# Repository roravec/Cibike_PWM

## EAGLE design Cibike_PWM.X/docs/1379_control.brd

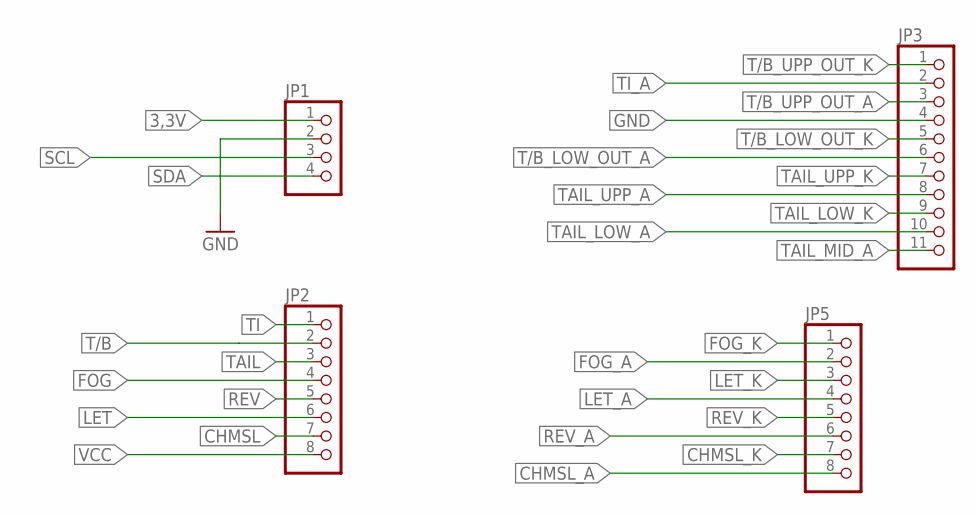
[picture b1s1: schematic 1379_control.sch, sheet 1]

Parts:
JP1: PINHD-1X4; 1X04
JP2, JP5: PINHD-1X8; 1X08
JP3: PINHD-1X11; 1X11

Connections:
3,3V: JP1.1; also elsewhere on the board
CHMSL: JP2.7; also elsewhere on the board
CHMSL_A: JP5.8; also elsewhere on the board
CHMSL_K: JP5.7; also elsewhere on the board
FOG: JP2.4; also elsewhere on the board
FOG_A: JP5.2; also elsewhere on the board
FOG_K: JP5.1; also elsewhere on the board
GND: JP1.2, JP3.4; also elsewhere on the board
LET: JP2.6; also elsewhere on the board
LET_A: JP5.4; also elsewhere on the board
LET_K: JP5.3; also elsewhere on the board
REV: JP2.5; also elsewhere on the board
REV_A: JP5.6; also elsewhere on the board
REV_K: JP5.5; also elsewhere on the board
SCL: JP1.3; also elsewhere on the board
SDA: JP1.4; also elsewhere on the board
T/B: JP2.2; also elsewhere on the board
T/B_LOW_OUT_A: JP3.6; also elsewhere on the board
T/B_LOW_OUT_K: JP3.5; also elsewhere on the board
T/B_UPP_OUT_A: JP3.3; also elsewhere on the board
T/B_UPP_OUT_K: JP3.1; also elsewhere on the board
TAIL: JP2.3; also elsewhere on the board
TAIL_LOW_A: JP3.10; also elsewhere on the board
TAIL_LOW_K: JP3.9; also elsewhere on the board
TAIL_MID_A: JP3.11; also elsewhere on the board
TAIL_UPP_A: JP3.8; also elsewhere on the board
TAIL_UPP_K: JP3.7; also elsewhere on the board
TI: JP2.1; also elsewhere on the board
TI_A: JP3.2; also elsewhere on the board
VCC: JP2.8; also elsewhere on the board

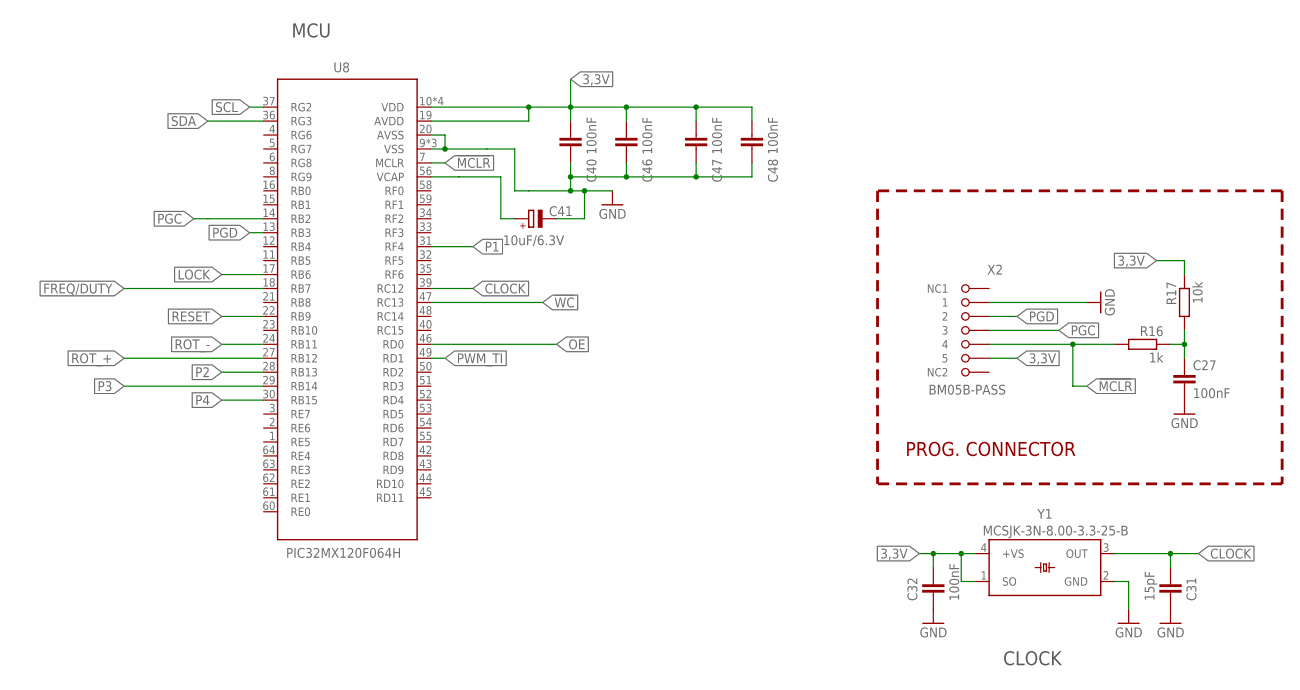
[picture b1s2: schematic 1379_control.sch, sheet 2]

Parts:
C27, C32, C40, C46, C47, C48: 100nF; C0603
C31: 15pF; C0603
C41: 10uF/6.3V; CT3216
R16: 1k; R0603
R17: 10k; R0603
U8: PIC32MX120F064H; PIC32MX-TQFN
X2: BM05B-PASS
Y1: MCSJK-3N-8.00-3.3-25-B; WE-SPXO_CFPS-104

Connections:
3,3V: C32.1, C40.1, C46.1, C47.1, C48.1, R17.1, U8.10 (VDD), U8.19 (AVDD), U8.26 (VDD), U8.38 (VDD), U8.57 (VDD), X2.P$5 (5), Y1.1 (SO), Y1.4 (+VS); also elsewhere on the board
!MCLR: R16.2, U8.7 (MCLR), X2.P$4 (4)
!WC: U8.47 (RC13); also elsewhere on the board
CLOCK: C31.1, U8.39 (RC12), Y1.3 (OUT)
FREQ/DUTY: U8.18 (RB7); also elsewhere on the board
GND: C27.2, C31.2, C32.2, C40.2, C41.-, C46.2, C47.2, C48.2, U8.9 (VSS), U8.20 (AVSS), U8.25 (VSS), U8.41 (VSS), X2.P$1 (1), Y1.2 (GND); also elsewhere on the board
LOCK: U8.17 (RB6); also elsewhere on the board
unnamed: C27.1, R16.1, R17.2
unnamed: C41.+, U8.56 (VCAP)
OE: U8.46 (RD0); also elsewhere on the board
P1: U8.31 (RF4); also elsewhere on the board
P2: U8.28 (RB13); also elsewhere on the board
P3: U8.29 (RB14); also elsewhere on the board
P4: U8.30 (RB15); also elsewhere on the board
PGC: U8.14 (RB2), X2.P$3 (3)
PGD: U8.13 (RB3), X2.P$2 (2)
PWM_TI: U8.49 (RD1); also elsewhere on the board
RE7: U8.3 (RE7)
RESET: U8.22 (RB9); also elsewhere on the board
ROT_+: U8.27 (RB12); also elsewhere on the board
ROT_-: U8.24 (RB11); also elsewhere on the board
SCL: U8.37 (RG2); also elsewhere on the board
SDA: U8.36 (RG3); also elsewhere on the board

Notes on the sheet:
PROG. CONNECTOR
MCU
CLOCK

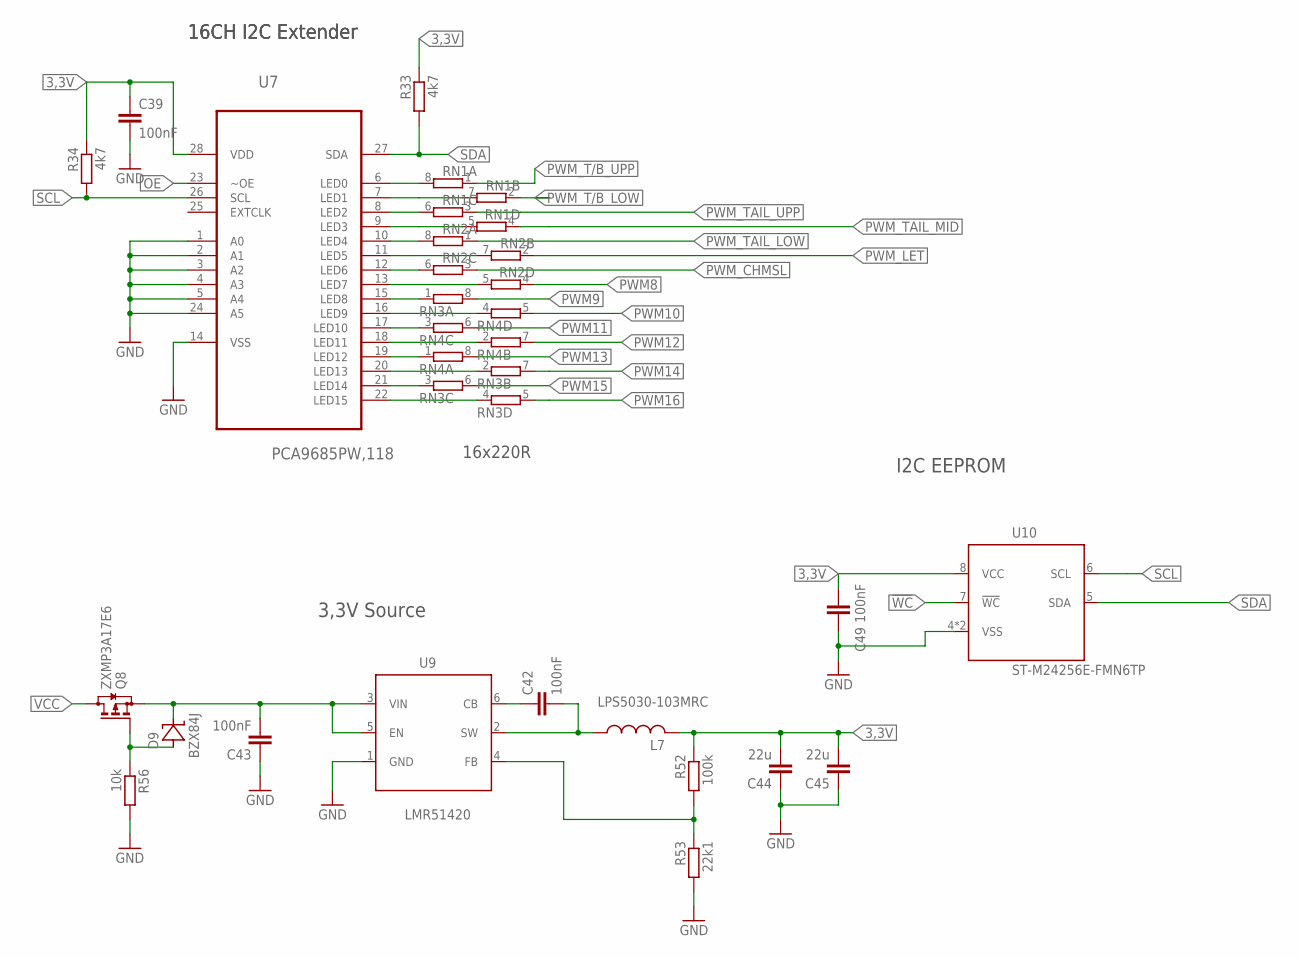
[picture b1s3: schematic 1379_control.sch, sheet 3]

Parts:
C39, C42, C43, C49: 100nF; C0603
C44, C45: 22u; C0603
D9: BZX84J; SOD323
L7: LPS5030-103MRC; L_5X5
Q8: ZXMP3A17E6; SOT23-6
R33, R34: 4k7; R0603
R52: 100k; R0603
R53: 22k1; R0603
R56: 10k; R0603
RN1, RN2, RN3, RN4: 4R-NEXBS8V; EXBS8V
U7: PCA9685PW,118; SOP65P640X110-28N
U9: LMR51420; SOT23-6
U10: ST-M24256E-FMN6TP; SO-8

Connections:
3,3V: C39.1, C44.2, C45.2, C49.1, L7.2, R33.1, R34.1, R52.1, U7.28 (VDD), U10.8 (VCC); also elsewhere on the board
!WC: U10.7 (!WC); also elsewhere on the board
GND: C39.2, C43.1, C44.1, C45.1, C49.2, R53.2, R56.2, U7.1 (A0), U7.2 (A1), U7.3 (A2), U7.4 (A3), U7.5 (A4), U7.14 (VSS), U7.24 (A5), U9.1 (GND), U10.4 (VSS), U10.EP (VSS); also elsewhere on the board
unnamed: RN1.8 (2), U7.6 (LED0)
unnamed: RN3.1, U7.15 (LED8)
unnamed: RN1.7 (2), U7.7 (LED1)
unnamed: RN4.4 (1), U7.16 (LED9)
unnamed: RN1.6 (2), U7.8 (LED2)
unnamed: RN4.3 (1), U7.17 (LED10)
unnamed: RN1.5 (2), U7.9 (LED3)
unnamed: RN2.8 (2), U7.10 (LED4)
unnamed: RN2.7 (2), U7.11 (LED5)
unnamed: RN2.6 (2), U7.12 (LED6)
unnamed: RN2.5 (2), U7.13 (LED7)
unnamed: RN4.2 (1), U7.18 (LED11)
unnamed: RN4.1, U7.19 (LED12)
unnamed: RN3.2 (1), U7.20 (LED13)
unnamed: RN3.3 (1), U7.21 (LED14)
unnamed: RN3.4 (1), U7.22 (LED15)
unnamed: R52.2, R53.1, U9.4 (FB)
unnamed: C42.2, L7.1, U9.2 (SW)
unnamed: C42.1, U9.6 (CB)
unnamed: D9.A, Q8.3 (G), R56.1
unnamed: C43.2, D9.C, Q8.4 (S), U9.3 (VIN), U9.5 (EN)
OE: U7.23 (~OE); also elsewhere on the board
PWM8: RN2.4 (1)
PWM9: RN3.8 (2)
PWM10: RN4.5 (2)
PWM11: RN4.6 (2)
PWM12: RN4.7 (2)
PWM13: RN4.8 (2)
PWM14: RN3.7 (2)
PWM15: RN3.6 (2)
PWM16: RN3.5 (2)
PWM_CHMSL: RN2.3 (1); also elsewhere on the board
PWM_LET: RN2.2 (1); also elsewhere on the board
PWM_T/B_LOW: RN1.2 (1); also elsewhere on the board
PWM_T/B_UPP: RN1.1; also elsewhere on the board
PWM_TAIL_LOW: RN2.1; also elsewhere on the board
PWM_TAIL_MID: RN1.4 (1); also elsewhere on the board
PWM_TAIL_UPP: RN1.3 (1); also elsewhere on the board
SCL: R34.2, U7.26 (SCL), U10.6 (SCL); also elsewhere on the board
SDA: R33.2, U7.27 (SDA), U10.5 (SDA); also elsewhere on the board
VCC: Q8.1 (D), Q8.2 (D), Q8.5 (D), Q8.6 (D); also elsewhere on the board

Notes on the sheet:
16x220R
16CH I2C Extender
I2C EEPROM
3,3V Source

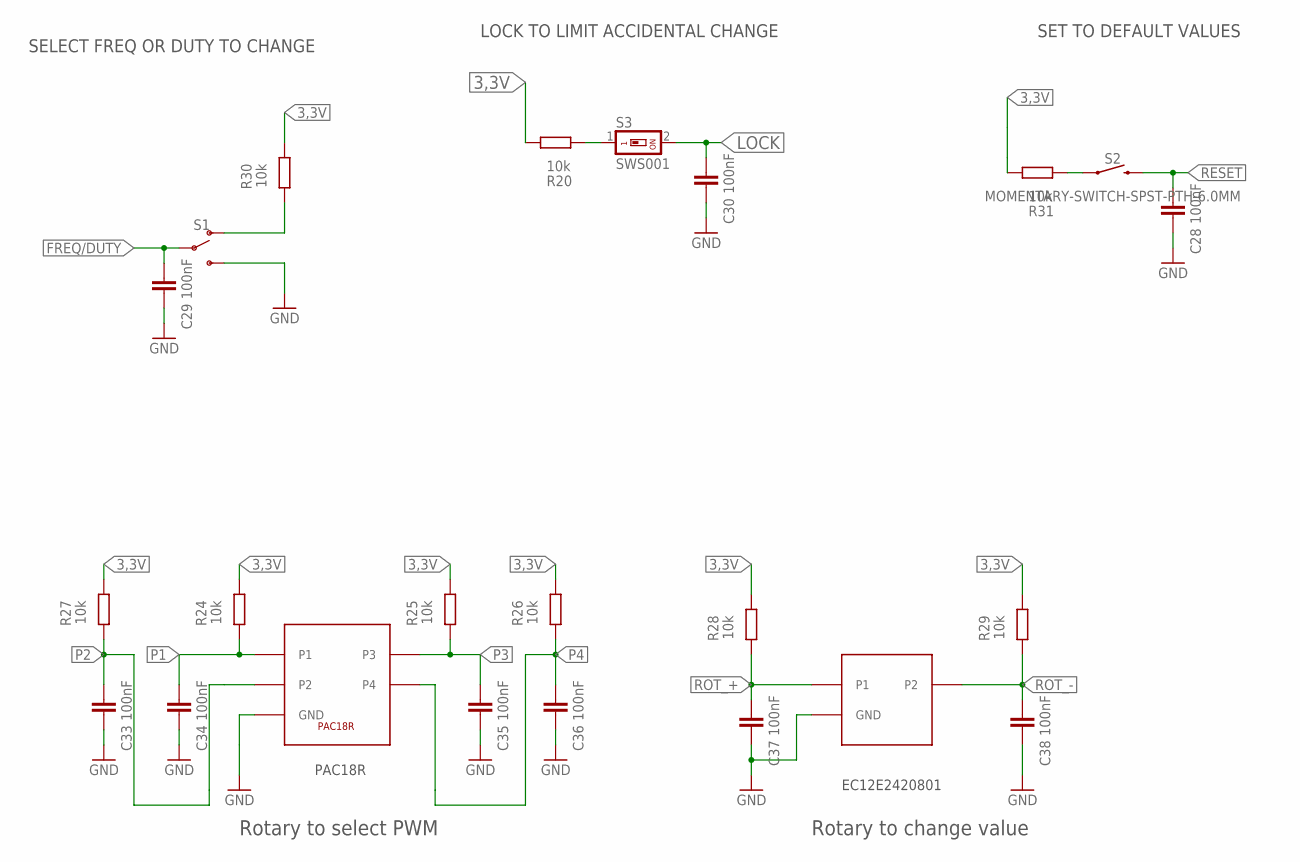
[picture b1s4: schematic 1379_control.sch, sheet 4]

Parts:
C28, C29, C30, C33, C34, C35, C36, C37, C38: 100nF; C0603
R20, R24, R25, R26, R27, R28, R29, R30, R31: 10k; R0603
S1: SWITCH-SPDT-PTH-11.6X4.0MM; SWITCH_SPDT_PTH_11.6X4.0MM
S2: MOMENTARY-SWITCH-SPST-PTH-6.0MM; TACTILE_SWITCH_PTH_6.0MM
S3: SWS001; SMS-001
X1: ENODER_ROTARY; ENCODER
X3: ENCODER-2

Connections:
3,3V: R20.1, R24.1, R25.1, R26.1, R27.1, R28.1, R29.1, R30.1, R31.1; also elsewhere on the board
FREQ/DUTY: C29.1, S1.2; also elsewhere on the board
GND: C28.2, C29.2, C30.2, C33.2, C34.2, C35.2, C36.2, C37.2, C38.2, S1.3 (S), X1.P$3 (GND), X3.P$2 (GND); also elsewhere on the board
LOCK: C30.1, S3.2; also elsewhere on the board
unnamed: R31.2, S2.1
unnamed: R30.2, S1.1 (O)
unnamed: R20.2, S3.1
P1: C34.1, R24.2, X1.P$5 (P1); also elsewhere on the board
P2: C33.1, R27.2, X1.P$1 (P2); also elsewhere on the board
P3: C35.1, R25.2, X1.P$4 (P3); also elsewhere on the board
P4: C36.1, R26.2, X1.P$2 (P4); also elsewhere on the board
RESET: C28.1, S2.3 (2); also elsewhere on the board
ROT_+: C37.1, R28.2, X3.P$1 (P1); also elsewhere on the board
ROT_-: C38.1, R29.2, X3.P$3 (P2); also elsewhere on the board

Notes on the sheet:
EC12E2420801
PAC18R
Rotary to select PWM
LOCK TO LIMIT ACCIDENTAL CHANGE
SELECT FREQ OR DUTY TO CHANGE
SET TO DEFAULT VALUES
Rotary to change value

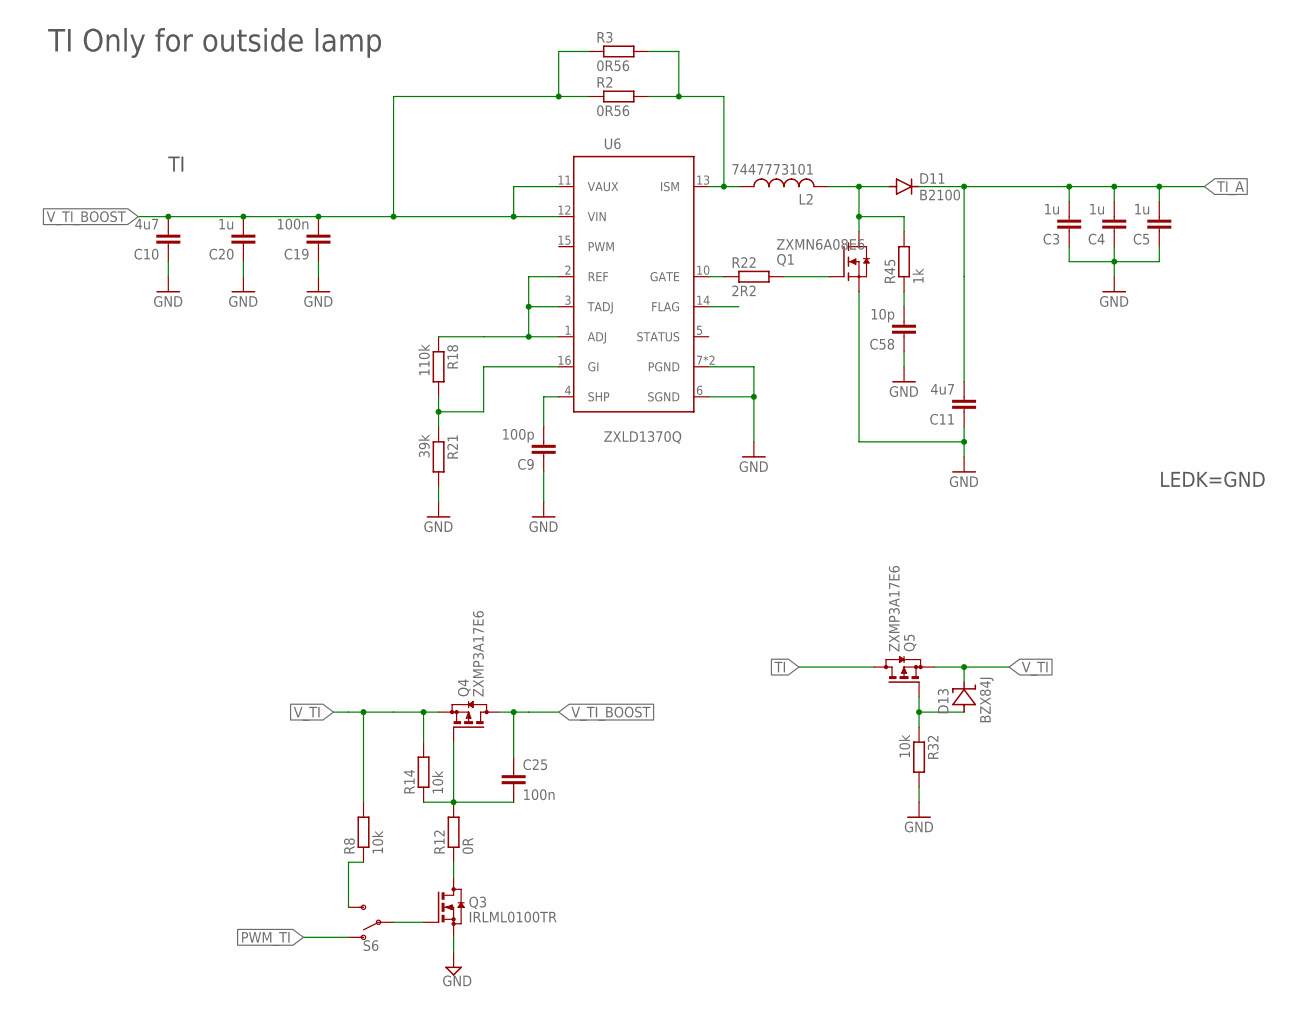
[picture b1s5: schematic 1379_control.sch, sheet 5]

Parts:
C3, C4, C5: 1u; C1206
C9: 100p; C0603
C10, C11: 4u7; C0603
C19, C25: 100n; C0603
C20: 1u; C0603
C58: 10p; C0603
D11: B2100; SMB
D13: BZX84J; SOD323
L2: 7447773101; L_7.4X7.4
Q1: ZXMN6A08E6; SOT23-6
Q3: IRLML0100TR; SOT23
Q4, Q5: ZXMP3A17E6; SOT23-6
R2, R3: 0R56; R0805
R8, R14, R32: 10k; R0603
R12: 0R; R0603
R18: 110k; R0603
R21: 39k; R0603
R22: 2R2; R0603
R45: 1k; R0603
S6: SWITCH-SPDT-PTH-11.6X4.0MM; SWITCH_SPDT_PTH_11.6X4.0MM
U6: ZXLD1370Q; TSSOP16E

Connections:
GND: C3.1, C4.1, C5.1, C9.1, C10.1, C11.1, C19.1, C20.1, C58.1, Q1.4 (S), Q3.2 (S), R21.2, R32.2, U6.6 (SGND), U6.7 (PGND), U6.EXP (PGND); also elsewhere on the board
unnamed: R8.1, S6.3 (S)
unnamed: C9.2, U6.4 (SHP)
unnamed: L2.1, R2.2, R3.2, U6.13 (ISM)
unnamed: D11.A, L2.2, Q1.1 (D), Q1.2 (D), Q1.5 (D), Q1.6 (D), R45.2
unnamed: R18.2, R21.1, U6.16 (GI)
unnamed: R18.1, U6.1 (ADJ), U6.2 (REF), U6.3 (TADJ)
unnamed: R22.1, U6.10 (GATE)
unnamed: Q1.3 (G), R22.2
unnamed: Q3.3 (D), R12.1
unnamed: C25.2, Q4.3 (G), R12.2, R14.1
unnamed: D13.A, Q5.3 (G), R32.1
unnamed: C58.2, R45.1
unnamed: Q3.1 (G), S6.2
PWM: U6.15 (PWM)
PWM_TI: S6.1 (O); also elsewhere on the board
TI: Q5.1 (D), Q5.2 (D), Q5.5 (D), Q5.6 (D); also elsewhere on the board
TI_A: C3.2, C4.2, C5.2, C11.2, D11.C; also elsewhere on the board
V_TI: D13.C, Q4.4 (S), Q5.4 (S), R8.2, R14.2
V_TI_BOOST: C10.2, C19.2, C20.2, C25.1, Q4.1 (D), Q4.2 (D), Q4.5 (D), Q4.6 (D), R2.1, R3.1, U6.11 (VAUX), U6.12 (VIN)

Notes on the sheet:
LEDK=GND
TI Only for outside lamp

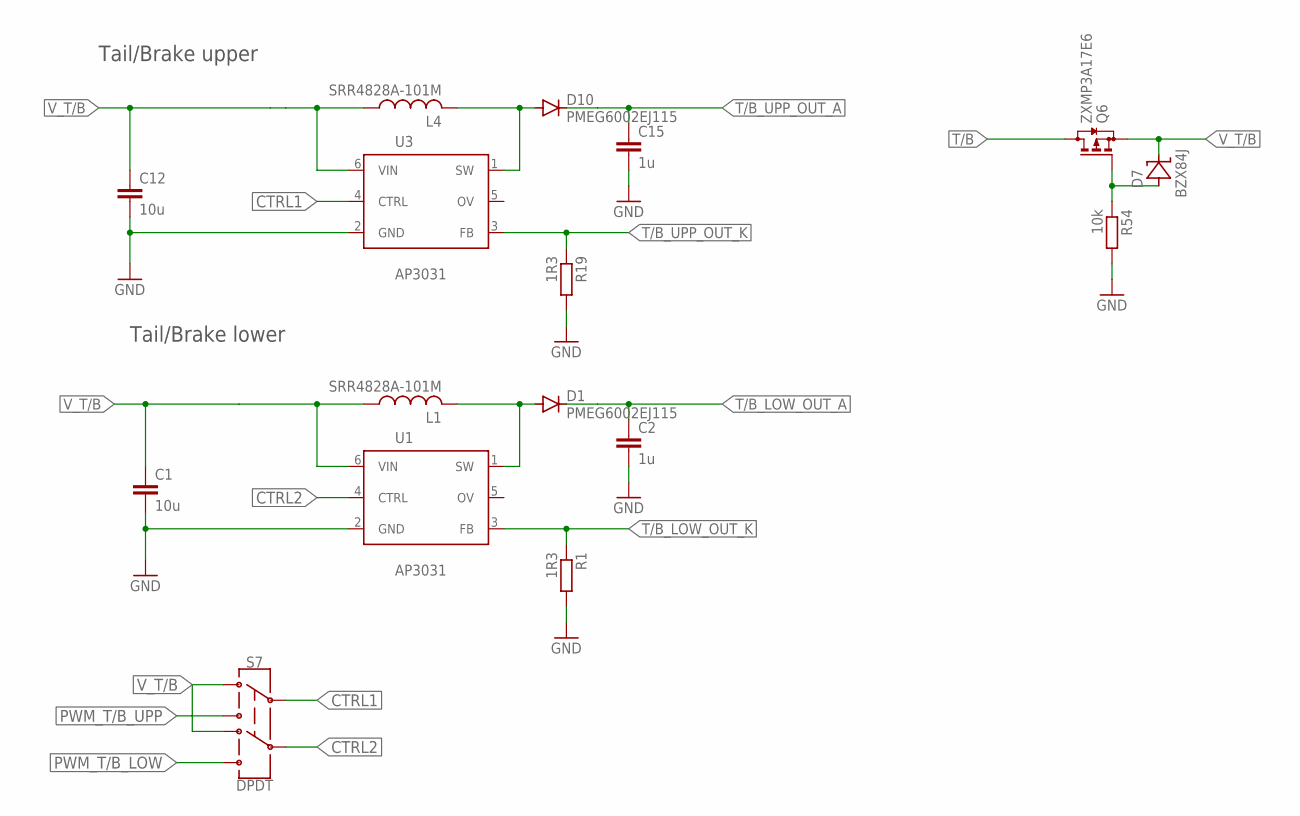
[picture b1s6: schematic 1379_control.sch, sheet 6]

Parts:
C1, C12: 10u; C0805
C2, C15: 1u; C0805
D1, D10: PMEG6002EJ115; SOD323-R
D7: BZX84J; SOD323
L1, L4: SRR4828A-101M; L_5X5
Q6: ZXMP3A17E6; SOT23-6
R1, R19: 1R3; R0805
R54: 10k; R0603
S7: DPDT; SWITCH_DPDT_PTH_GPI-152-3013
U1, U3: AP3031; SOT23-6

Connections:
CTRL1: S7.C@1 (2), U3.4 (CTRL)
CTRL2: S7.C@2 (5), U1.4 (CTRL)
GND: C1.2, C2.2, C12.2, C15.2, R1.2, R19.2, R54.2, U1.2 (GND), U3.2 (GND); also elsewhere on the board
unnamed: D1.A, L1.2, U1.1 (SW)
unnamed: D10.A, L4.2, U3.1 (SW)
unnamed: D7.A, Q6.3 (G), R54.1
PWM_T/B_LOW: S7.21 (6); also elsewhere on the board
PWM_T/B_UPP: S7.11 (3); also elsewhere on the board
T/B: Q6.1 (D), Q6.2 (D), Q6.5 (D), Q6.6 (D); also elsewhere on the board
T/B_LOW_OUT_A: C2.1, D1.C; also elsewhere on the board
T/B_LOW_OUT_K: R1.1, U1.3 (FB); also elsewhere on the board
T/B_UPP_OUT_A: C15.1, D10.C; also elsewhere on the board
T/B_UPP_OUT_K: R19.1, U3.3 (FB); also elsewhere on the board
V_T/B: C1.1, C12.1, D7.C, L1.1, L4.1, Q6.4 (S), S7.10 (1), S7.20 (4), U1.6 (VIN), U3.6 (VIN)

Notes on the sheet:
Tail/Brake upper
Tail/Brake lower

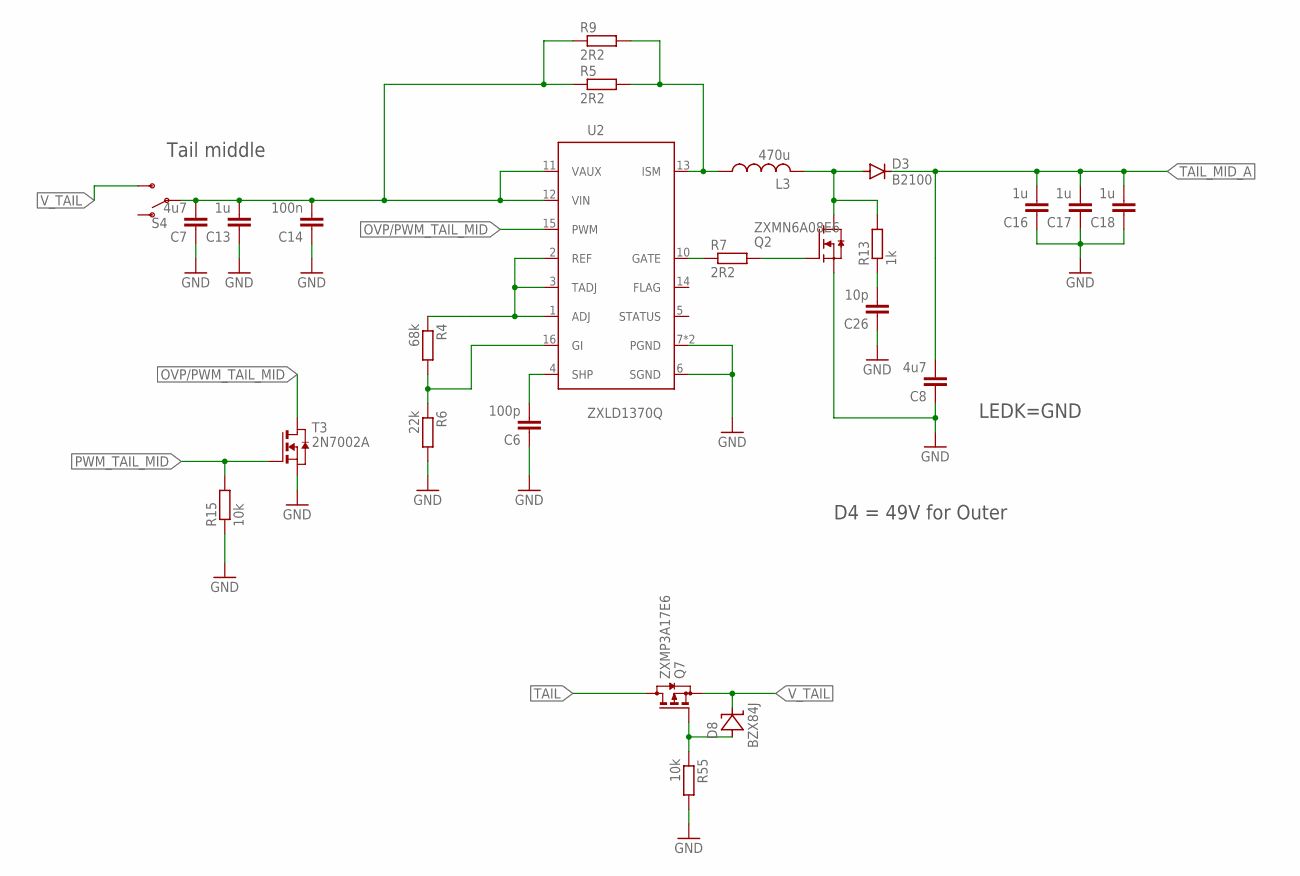
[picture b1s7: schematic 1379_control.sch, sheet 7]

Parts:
C6: 100p; C0603
C7, C8: 4u7; C0603
C13: 1u; C0603
C14: 100n; C0603
C16, C17, C18: 1u; C1206
C26: 10p; C0603
D3: B2100; SMB
D8: BZX84J; SOD323
L3: 470u; L_7.4X7.4
Q2: ZXMN6A08E6; SOT23-6
Q7: ZXMP3A17E6; SOT23-6
R4: 68k; R0603
R5, R9: 2R2; R0805
R6: 22k; R0603
R7: 2R2; R0603
R13: 1k; R0603
R15, R55: 10k; R0603
S4: SWITCH-SPDT-PTH-11.6X4.0MM; SWITCH_SPDT_PTH_11.6X4.0MM
T3: 2N7002A; SOT-23
U2: ZXLD1370Q; TSSOP16E

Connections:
FLAG: U2.14 (FLAG)
GND: C6.1, C7.1, C8.1, C13.1, C14.1, C16.1, C17.1, C18.1, C26.1, Q2.4 (S), R6.2, R15.1, R55.2, T3.2 (S), U2.6 (SGND), U2.7 (PGND), U2.EXP (PGND); also elsewhere on the board
unnamed: C6.2, U2.4 (SHP)
unnamed: L3.1, R5.2, R9.2, U2.13 (ISM)
unnamed: D3.A, L3.2, Q2.1 (D), Q2.2 (D), Q2.5 (D), Q2.6 (D), R13.2
unnamed: R4.2, R6.1, U2.16 (GI)
unnamed: R4.1, U2.1 (ADJ), U2.2 (REF), U2.3 (TADJ)
unnamed: R7.1, U2.10 (GATE)
unnamed: Q2.3 (G), R7.2
unnamed: C26.2, R13.1
unnamed: D8.A, Q7.3 (G), R55.1
OVP/PWM_TAIL_MID: T3.1 (D), U2.15 (PWM)
PWM_TAIL_MID: R15.2, T3.3 (G); also elsewhere on the board
TAIL: Q7.1 (D), Q7.2 (D), Q7.5 (D), Q7.6 (D); also elsewhere on the board
TAIL_MID_A: C8.2, C16.2, C17.2, C18.2, D3.C; also elsewhere on the board
V_TAIL: D8.C, Q7.4 (S), S4.3 (S); also elsewhere on the board
V_TAIL1: C7.2, C13.2, C14.2, R5.1, R9.1, S4.2, U2.11 (VAUX), U2.12 (VIN)

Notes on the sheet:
LEDK=GND
Tail middle
D4 = 49V for Outer

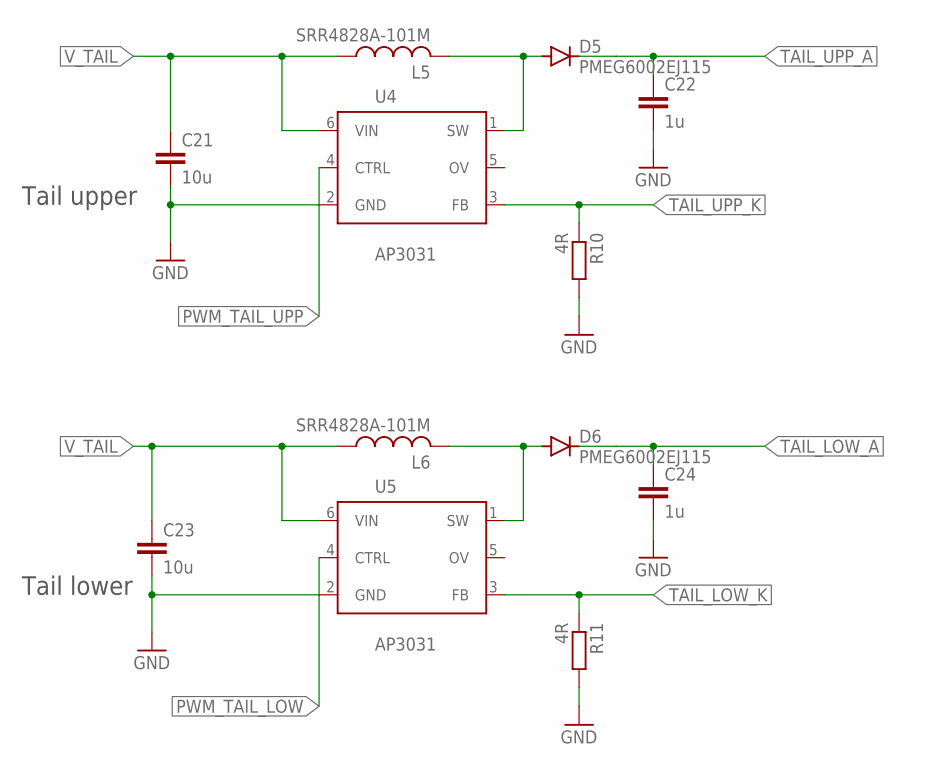
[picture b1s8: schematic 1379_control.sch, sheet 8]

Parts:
C21, C23: 10u; C0805
C22, C24: 1u; C0805
D5, D6: PMEG6002EJ115; SOD323-R
L5, L6: SRR4828A-101M; L_5X5
R10, R11: 4R; R0805
U4, U5: AP3031; SOT23-6

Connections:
GND: C21.2, C22.2, C23.2, C24.2, R10.2, R11.2, U4.2 (GND), U5.2 (GND); also elsewhere on the board
unnamed: D5.A, L5.2, U4.1 (SW)
unnamed: D6.A, L6.2, U5.1 (SW)
PWM_TAIL_LOW: U5.4 (CTRL); also elsewhere on the board
PWM_TAIL_UPP: U4.4 (CTRL); also elsewhere on the board
TAIL_LOW_A: C24.1, D6.C; also elsewhere on the board
TAIL_LOW_K: R11.1, U5.3 (FB); also elsewhere on the board
TAIL_UPP_A: C22.1, D5.C; also elsewhere on the board
TAIL_UPP_K: R10.1, U4.3 (FB); also elsewhere on the board
V_TAIL: C21.1, C23.1, L5.1, L6.1, U4.6 (VIN), U5.6 (VIN); also elsewhere on the board

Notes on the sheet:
Tail upper
Tail lower

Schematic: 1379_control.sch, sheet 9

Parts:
C50, C52: 10u; C0805
C51, C53: 1u; C0805
D12, D14: PMEG6002EJ115; SOD323-R
D17, D18: BZX84J; SOD323
L8, L9: SRR4828A-101M; L_5X5
Q9, Q10: ZXMP3A17E6; SOT23-6
R37: 1R05; R0805
R38: 1R43; R0805
R41, R42: 10k; R0603
U11, U12: AP3031; SOT23-6

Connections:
FOG: Q9.1 (D), Q9.2 (D), Q9.5 (D), Q9.6 (D); also elsewhere on the board
FOG_A: C51.1, D12.C; also elsewhere on the board
FOG_K: R37.1, U11.3 (FB); also elsewhere on the board
GND: C50.2, C51.2, C52.2, C53.2, R37.2, R38.2, R41.2, R42.2, U11.2 (GND), U12.2 (GND); also elsewhere on the board
unnamed: D12.A, L8.2, U11.1 (SW)
unnamed: D14.A, L9.2, U12.1 (SW)
unnamed: D17.A, Q9.3 (G), R41.1
unnamed: D18.A, Q10.3 (G), R42.1
REV: Q10.1 (D), Q10.2 (D), Q10.5 (D), Q10.6 (D); also elsewhere on the board
REV_A: C53.1, D14.C; also elsewhere on the board
REV_K: R38.1, U12.3 (FB); also elsewhere on the board
V_FOG: C50.1, D17.C, L8.1, Q9.4 (S), U11.6 (VIN)
V_REV: C52.1, D18.C, L9.1, Q10.4 (S), U12.6 (VIN)

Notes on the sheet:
Fog
Reverse
Only for middle

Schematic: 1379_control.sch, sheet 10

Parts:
C54, C56: 10u; C0805
C55, C57: 1u; C0805
D15, D16: PMEG6002EJ115; SOD323-R
D19, D20: BZX84J; SOD323
L10, L11: SRR4828A-101M; L_5X5
Q11, Q12: ZXMP3A17E6; SOT23-6
R39: 6R6; R0805
R40: 2R2; R0805
R43, R44: 10k; R0603
U13, U14: AP3031; SOT23-6

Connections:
CHMSL: Q12.1 (D), Q12.2 (D), Q12.5 (D), Q12.6 (D); also elsewhere on the board
CHMSL_A: C57.1, D16.C; also elsewhere on the board
CHMSL_K: R40.1, U14.3 (FB); also elsewhere on the board
GND: C54.2, C55.2, C56.2, C57.2, R39.2, R40.2, R43.2, R44.2, U13.2 (GND), U14.2 (GND); also elsewhere on the board
LET: Q11.1 (D), Q11.2 (D), Q11.5 (D), Q11.6 (D); also elsewhere on the board
LET_A: C55.1, D15.C; also elsewhere on the board
LET_K: R39.1, U13.3 (FB); also elsewhere on the board
unnamed: D15.A, L10.2, U13.1 (SW)
unnamed: D16.A, L11.2, U14.1 (SW)
unnamed: D19.A, Q11.3 (G), R43.1
unnamed: D20.A, Q12.3 (G), R44.1
PWM_CHMSL: U14.4 (CTRL); also elsewhere on the board
PWM_LET: U13.4 (CTRL); also elsewhere on the board
V_CHMSL: C56.1, D20.C, L11.1, Q12.4 (S), U14.6 (VIN)
V_LET: C54.1, D19.C, L10.1, Q11.4 (S), U13.6 (VIN)

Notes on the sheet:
Lettering
CHMSL
Only for middle

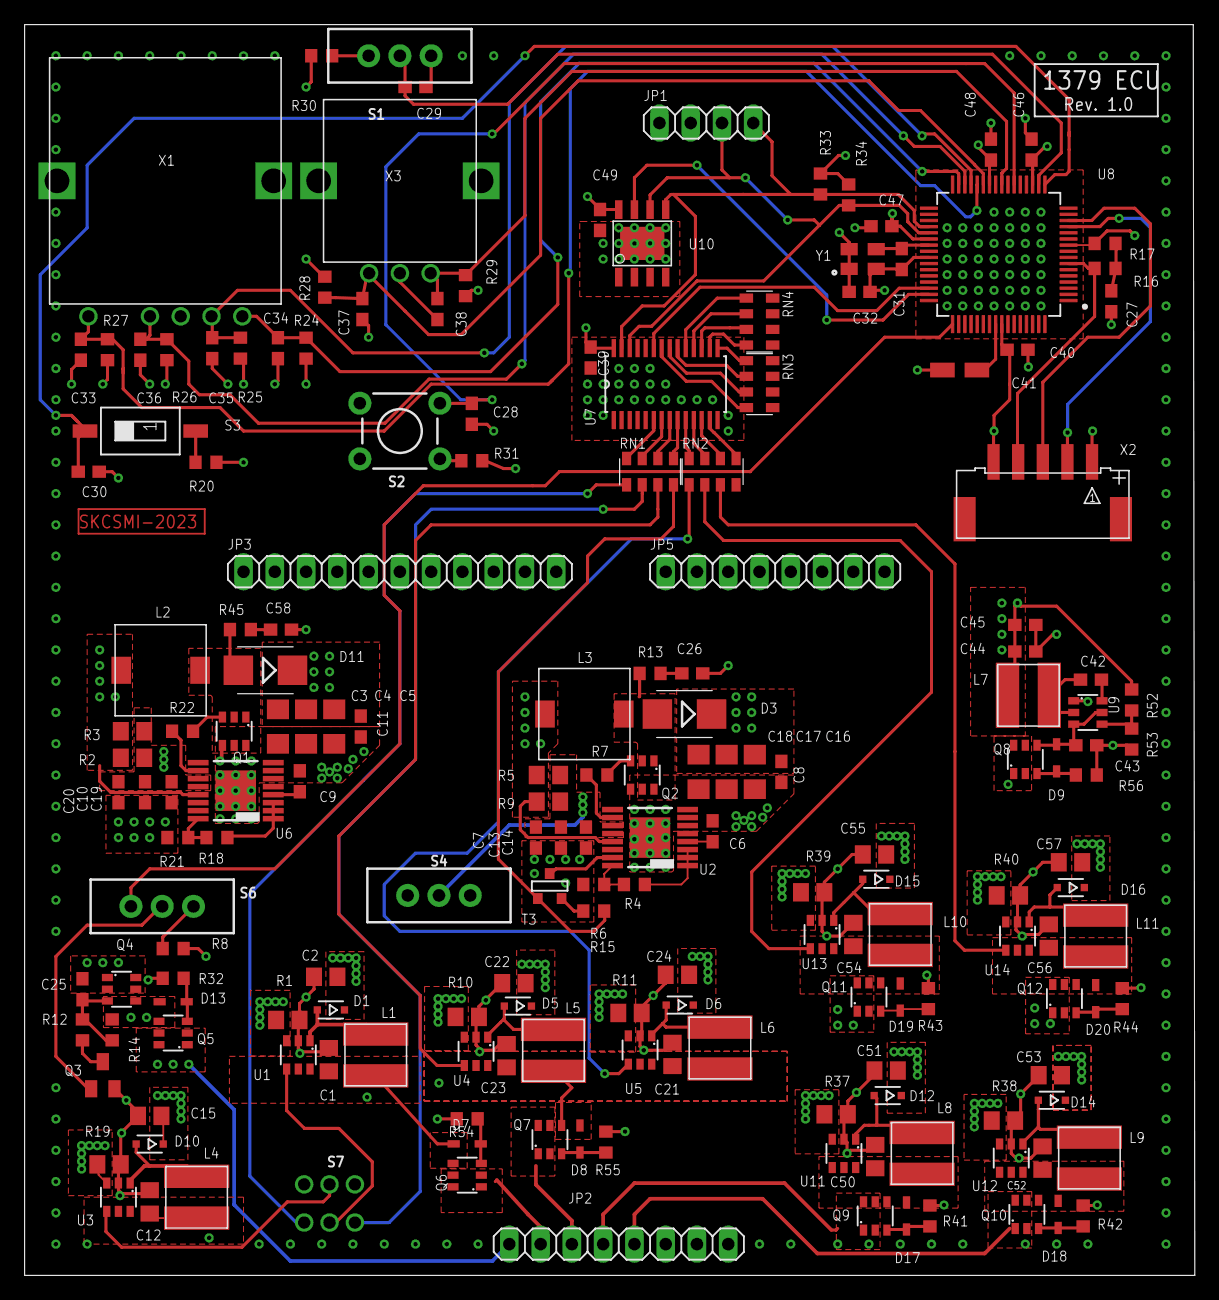
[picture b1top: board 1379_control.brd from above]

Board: 4 copper layers, 95.0 x 101.6 mm, 179 parts (0 on the bottom side), 126 nets.

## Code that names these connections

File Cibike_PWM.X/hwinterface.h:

/* 
 * File:   hwinterface.h
 * Author: skorra
 *
 * Created on March 29, 2023, 2:03 PM
 */

#ifndef HWINTERFACE_H
#define	HWINTERFACE_H

#include <xc.h>

#define HW_ROTARY_PLUS_TRIS     TRISBbits.TRISB12  
#define HW_ROTARY_PLUS_PORT     PORTBbits.RB12
#define HW_ROTARY_PLUS_LAT      LATBbits.LATB12
#define HW_ROTARY_MINUS_TRIS    TRISBbits.TRISB11 
#define HW_ROTARY_MINUS_PORT    PORTBbits.RB11
#define HW_ROTARY_MINUS_LAT     LATBbits.LATB11

#define HW_POS1_TRIS            TRISFbits.TRISF4
#define HW_POS1_PORT            PORTFbits.RF4
#define HW_POS1_LAT             LATFbits.LATF4
#define HW_POS2_TRIS            TRISBbits.TRISB13 
#define HW_POS2_PORT            PORTBbits.RB13
#define HW_POS2_LAT             LATBbits.LATB13
#define HW_POS3_TRIS            TRISBbits.TRISB14 
#define HW_POS3_PORT            PORTBbits.RB14
#define HW_POS3_LAT             LATBbits.LATB14
#define HW_POS4_TRIS            TRISBbits.TRISB15 
#define HW_POS4_PORT            PORTBbits.RB15
#define HW_POS4_LAT             LATBbits.LATB15

#define HW_LOCK_TRIS            TRISBbits.TRISB6
#define HW_LOCK_PORT            PORTBbits.RB6
#define HW_LOCK_LAT             LATBbits.LATB6
#define HW_RESET_TRIS           TRISBbits.TRISB9
#define HW_RESET_PORT           PORTBbits.RB9
#define HW_RESET_LAT            LATBbits.LATB9

#define HW_FREQ_DUTY_TRIS       TRISBbits.TRISB7
#define HW_FREQ_DUTY_PORT       PORTBbits.RB7
#define HW_FREQ_DUTY_LAT        LATBbits.LATB7

#define HW_MEMORY_ENABLE_TRIS   TRISCbits.TRISC13
#define HW_MEMORY_ENABLE_PORT   PORTCbits.RC13
#define HW_MEMORY_ENABLE_LAT    LATCbits.LATC13
#define HW_PWMCON_ENABLE_TRIS   TRISDbits.TRISD0
#define HW_PWMCON_ENABLE_PORT   PORTDbits.RD0
#define HW_PWMCON_ENABLE_LAT    LATDbits.LATD0

#define HW_TI_OUT_TRIS          TRISDbits.TRISD1
#define HW_TI_OUT_PORT          PORTDbits.RD1
#define HW_TI_OUT_LAT           LATDbits.LATD1


#ifdef	__cplusplus
extern "C" {
#endif

    void HW_Init(void);

#ifdef	__cplusplus
}
#endif

#endif	/* HWINTERFACE_H */

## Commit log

2023-04-03 Init
2023-04-03 init 2
2023-04-13 Work in progress
2023-04-14 New layout
2023-04-20 PWM works
2023-04-23 Final
2023-04-24 Final 2

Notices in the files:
parts and their libraries:
SparkFun-Switches: Licensing: Creative Commons ShareAlike 4.0 International - https://creativecommons.org/licenses/by-sa/4.0
Wurth_Quartz Crystals: Copyright: Würth Elektronik
